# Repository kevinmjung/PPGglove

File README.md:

# PPGglove
This is a repository with the devices and guides corresponding to the device. It will be regularly updated or if there are specific updates that you want to be pushed 
please email me at: kmjung@ucla.edu

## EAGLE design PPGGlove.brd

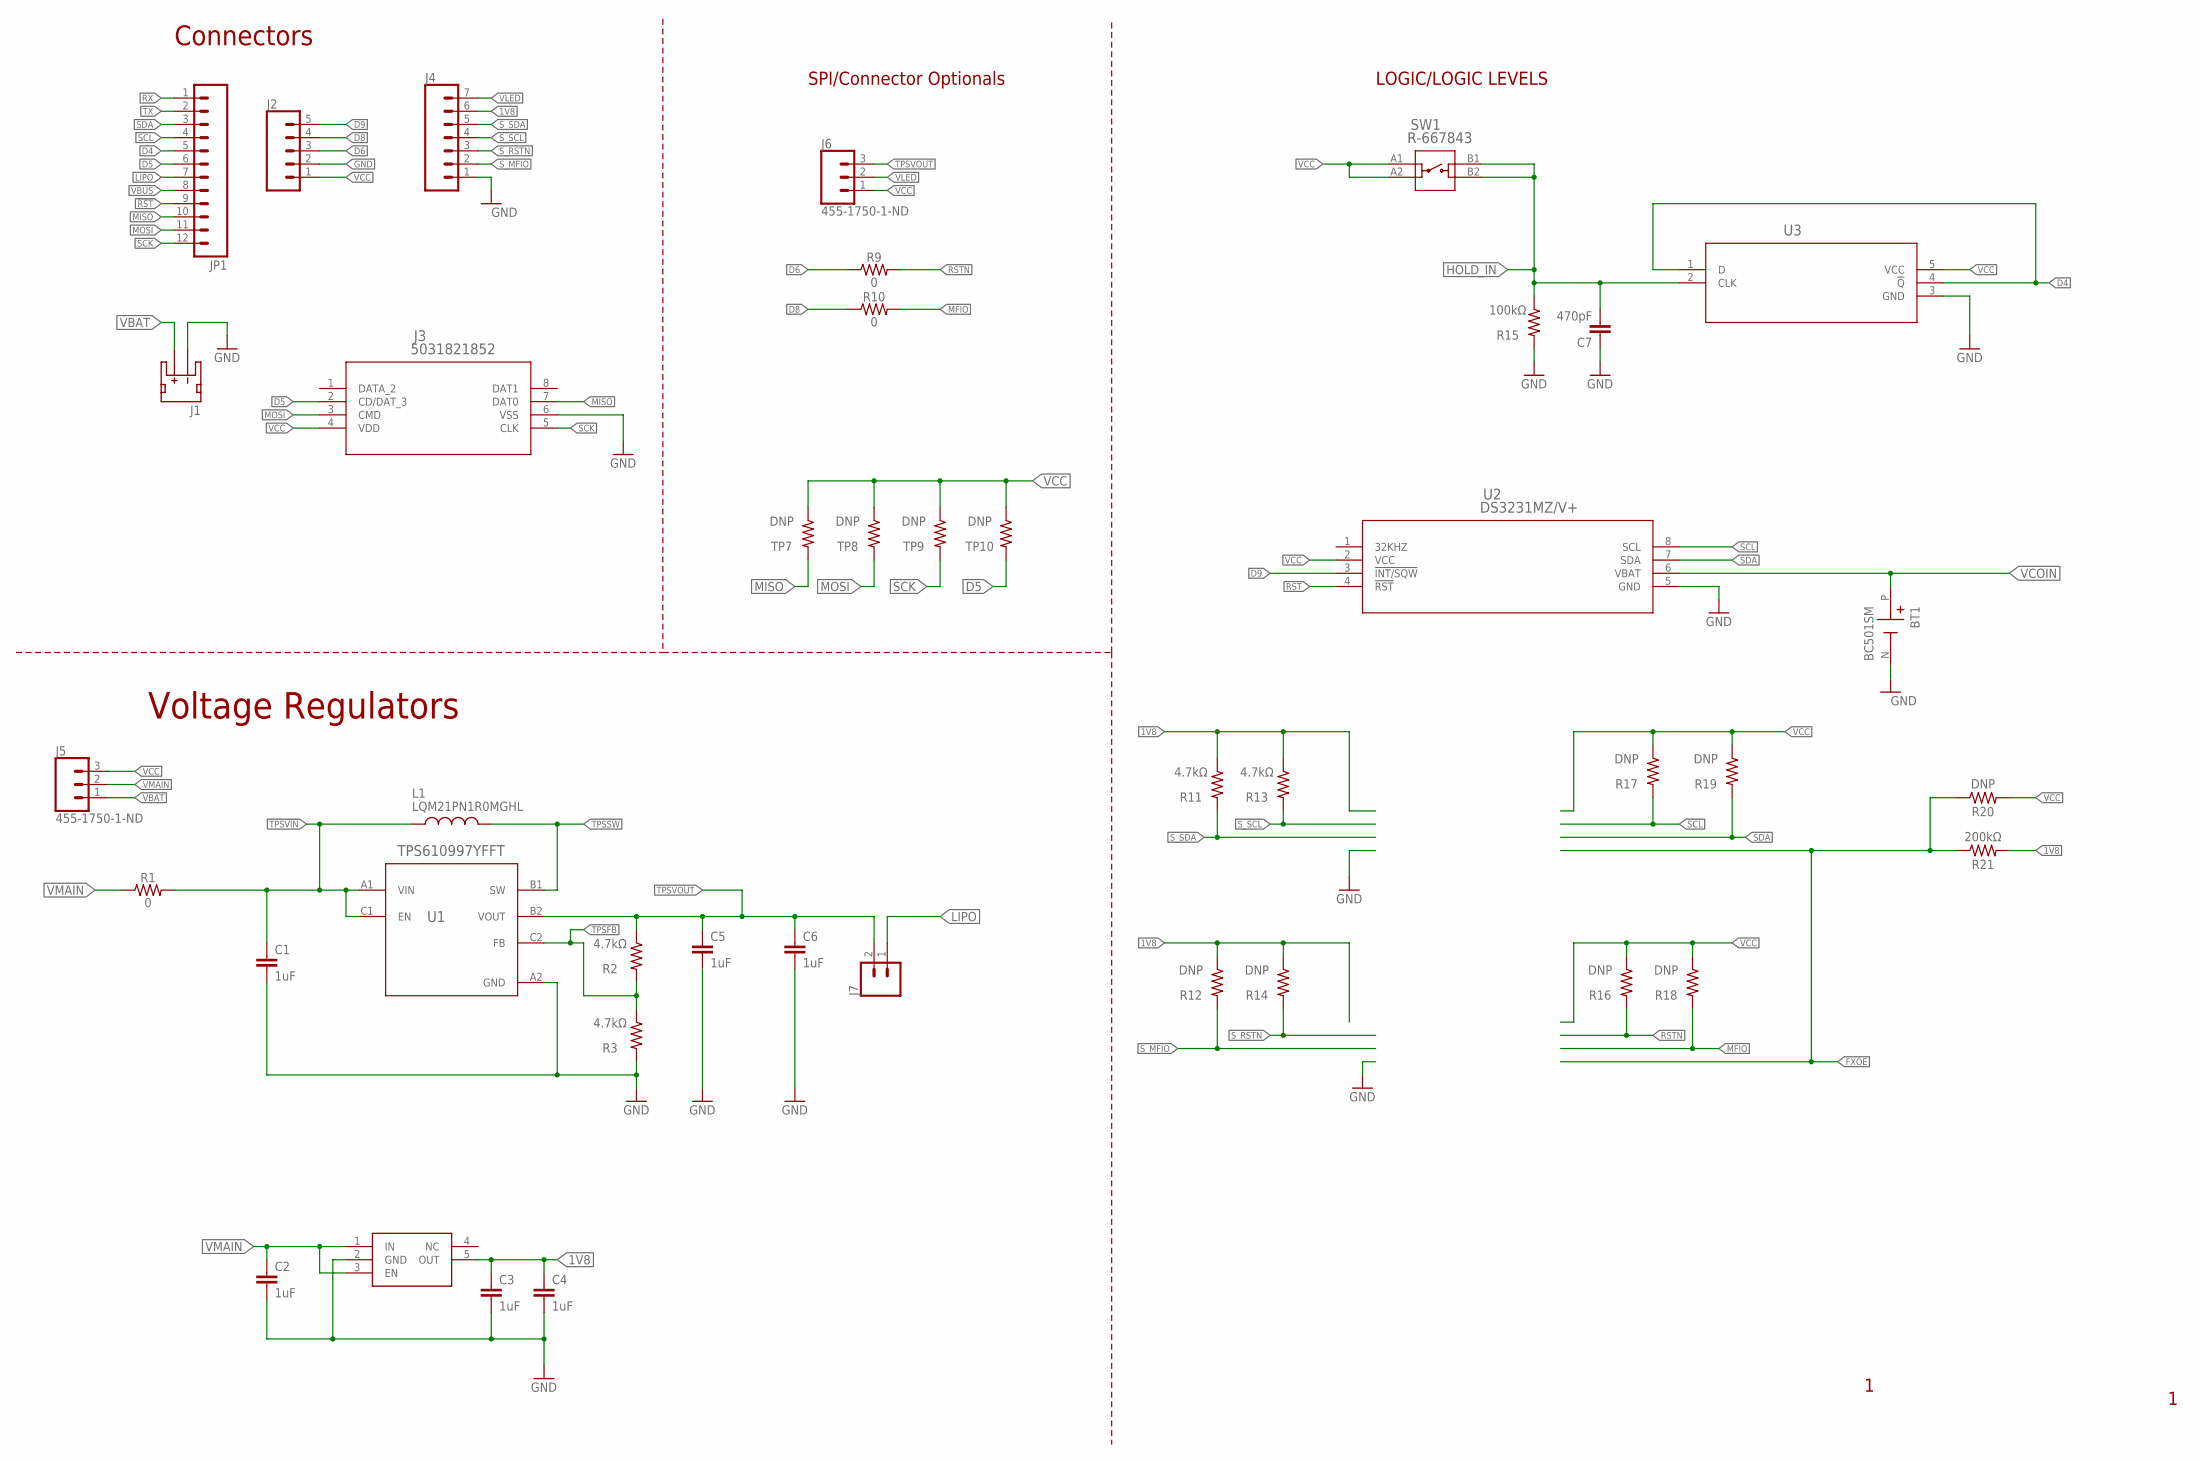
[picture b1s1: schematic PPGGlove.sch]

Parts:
BT1: BC501SM; BAT_BC501SM
C1, C2, C3, C4, C5, C6: 1uF; 0805
C7: 470pF; 0805
IC1: TPS7A0318DBVR; SOT95P280X145-5N
J1: JST_2MM_MALE; JST-2-SMD
J2: CONN_05; 1X05
J3: 5031821852; 503182-1852_MOL
J4: CONN_07; 1X07
J5, J6: 455-1750-1-ND; 1X03
J7: CONN_02; 1X02
JP1: M12PTH; 1X12
L1: LQM21PN1R0MGHL; INDC2012X100N
R1, R9, R10: 0; 0805
R2, R3, R11, R13: 4.7kΩ; 0805
R12, R14, R16, R17, R18, R19, R20: DNP; 0805
R15: 100kΩ; 0805
R21: 200kΩ; 0805
SW1: R-667843; R-667843_MIT
TP7, TP8, TP9, TP10: DNP; 0805
U1: TPS610997YFFT; YFF0006AFAD
U2: DS3231MZ/V+; 21-0041B_8_MXM
U5: U3; DBV5

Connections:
1V8: C3.1, C4.1, IC1.5 (OUT), J4.6, R11.1, R12.1, R13.1, R14.1, R21.2
!RST: JP1.9
D4: JP1.5, U5.1 (D), U5.4 (!Q)
D5: J3.2 (CD/DAT_3), JP1.6, TP10.2
D6: J2.3, R9.1
D8: J2.4, R10.1
D9: J2.5, U2.3 (!INT/SQW)
FXOE: R20.1, R21.1
GND: BT1.N (-), C1.2, C2.2, C3.2, C4.2, C5.2, C6.2, C7.1, IC1.2 (GND), J1.1 (-), J2.2, J3.6 (VSS), J4.1, R3.2, R15.2, U1.A2 (GND), U2.5 (GND), U5.3 (GND)
HOLD_IN: C7.2, R15.1, SW1.B1, SW1.B2, U5.2 (CLK)
LIPO: J7.1, JP1.7
MFIO: R10.2, R18.2
MISO: J3.7 (DAT0), JP1.10, TP7.2
MOSI: J3.3 (CMD), JP1.11, TP8.2
RST: U2.4 (!RST)
RSTN: R9.2, R16.2
RX: JP1.1
SCK: J3.5 (CLK), JP1.12, TP9.2
SCL: JP1.4, R17.2, U2.8 (SCL)
SDA: JP1.3, R19.2, U2.7 (SDA)
S_MFIO: J4.2, R12.2
S_RSTN: J4.3, R14.2
S_SCL: J4.4, R13.2
S_SDA: J4.5, R11.2
TPSFB: R2.2, R3.1, U1.C2 (FB)
TPSSW: L1.2, U1.B1 (SW)
TPSVIN: C1.1, L1.1, R1.2, U1.A1 (VIN), U1.C1 (EN)
TPSVOUT: C5.1, C6.1, J6.3, J7.2, R2.1, U1.B2 (VOUT)
TX: JP1.2
VBAT: J1.2 (+), J5.1
VBUS: JP1.8
VCC: J2.1, J3.4 (VDD), J5.3, J6.1, R16.1, R17.1, R18.1, R19.1, R20.2, SW1.A1, SW1.A2, TP7.1, TP8.1, TP9.1, TP10.1, U2.2 (VCC), U5.5 (VCC)
VCOIN: BT1.P (+), U2.6 (VBAT)
VLED: J4.7, J6.2
VMAIN: C2.1, IC1.1 (IN), IC1.3 (EN), J5.2, R1.1

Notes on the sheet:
Connectors
Voltage Regulators
SPI/Connector Optionals
LOGIC/LOGIC LEVELS

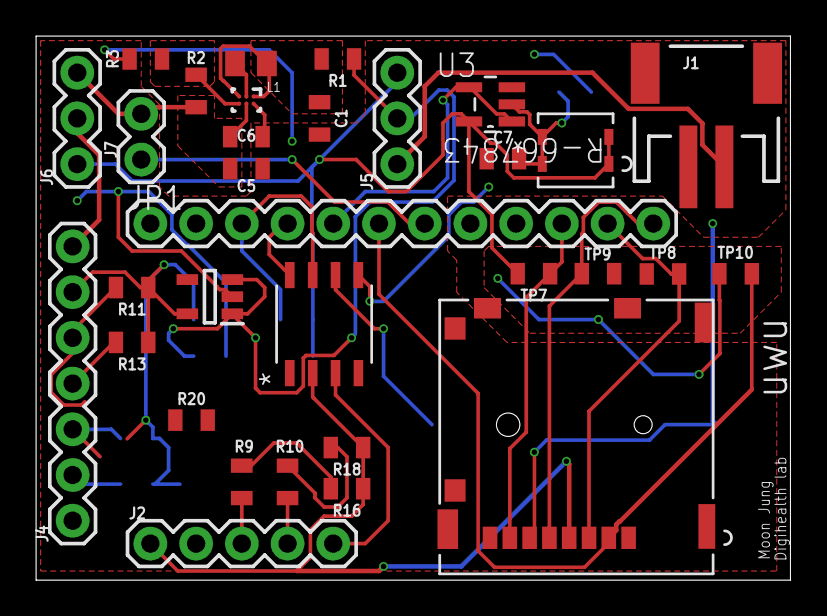
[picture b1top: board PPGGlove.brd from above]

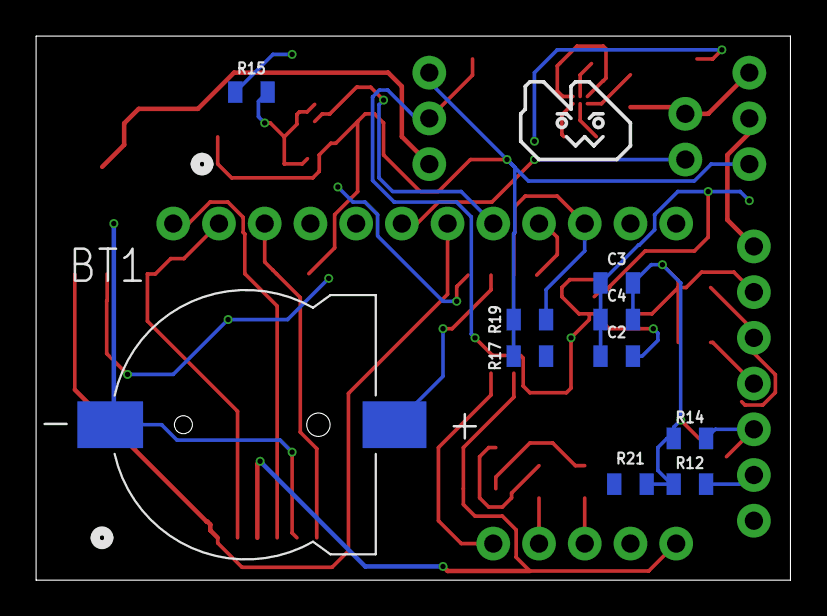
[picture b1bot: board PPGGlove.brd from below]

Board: 2 copper layers, 41.9 x 30.2 mm, 42 parts (10 on the bottom side), 30 nets.

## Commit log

2022-10-06 Add files via upload
    right images

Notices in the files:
PPGGlove.brd:
Copyright (c) 2016-2017 Arduino LLC.  All right reserved. EAGLE Design Rules
parts and their libraries:
SparkFun-Connectors: Licensing: Creative Commons ShareAlike 4.0 International - https://creativecommons.org/licenses/by-sa/4.0
COPYRIGHT: Copyright (C) 2022 Ultra Librarian. All rights reserved.
